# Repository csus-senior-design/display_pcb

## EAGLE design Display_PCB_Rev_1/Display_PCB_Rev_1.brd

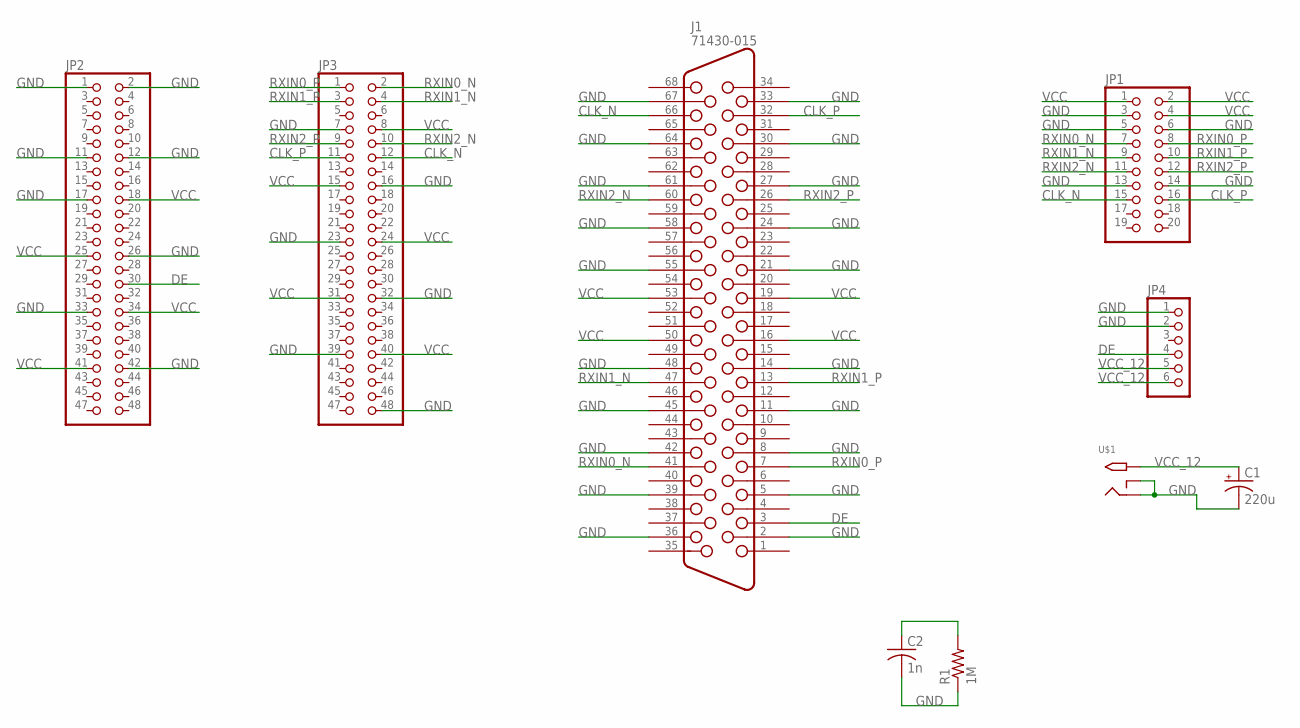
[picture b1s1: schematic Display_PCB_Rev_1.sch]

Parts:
C1: 220u; E5-8,5
C2: 1n; C0805
J1: 71430-015
JP1: PINHD-2X10M; 2X10M
JP2, JP3: PINHD-2X24; 2X24
JP4: PINHD-1X6M; 1X06M
R1: 1M; R0805W
U$1: 2.1MMJACKTHM; PJ-102A

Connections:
CLK_N: J1.66, JP1.15, JP3.12
CLK_P: J1.32, JP1.16, JP3.11
DE: J1.3, JP2.30, JP4.4
GND: C1.-, C2.2, J1.2, J1.5, J1.8, J1.11, J1.14, J1.21, J1.24, J1.27, J1.30, J1.33, J1.36, J1.39, J1.42, J1.45, J1.48, J1.55, J1.58, J1.61, J1.64, J1.67, JP1.3, JP1.5, JP1.6, JP1.13, JP1.14, JP2.1, JP2.2, JP2.11, JP2.12, JP2.17, JP2.26, JP2.33, JP2.42, JP3.7, JP3.16, JP3.23, JP3.32, JP3.39, JP3.48, JP4.1, JP4.2, R1.1, U$1.RING, U$1.RING_SW
unnamed: C2.1, R1.2
RXIN0_N: J1.41, JP1.7, JP3.2
RXIN0_P: J1.7, JP1.8, JP3.1
RXIN1_N: J1.47, JP1.9, JP3.4
RXIN1_P: J1.13, JP1.10, JP3.3
RXIN2_N: J1.60, JP1.11, JP3.10
RXIN2_P: J1.26, JP1.12, JP3.9
VCC: J1.16, J1.19, J1.50, J1.53, JP1.1, JP1.2, JP1.4, JP2.18, JP2.25, JP2.34, JP2.41, JP3.8, JP3.15, JP3.24, JP3.31, JP3.40
VCC_12: C1.+, JP4.5, JP4.6, U$1.TIP

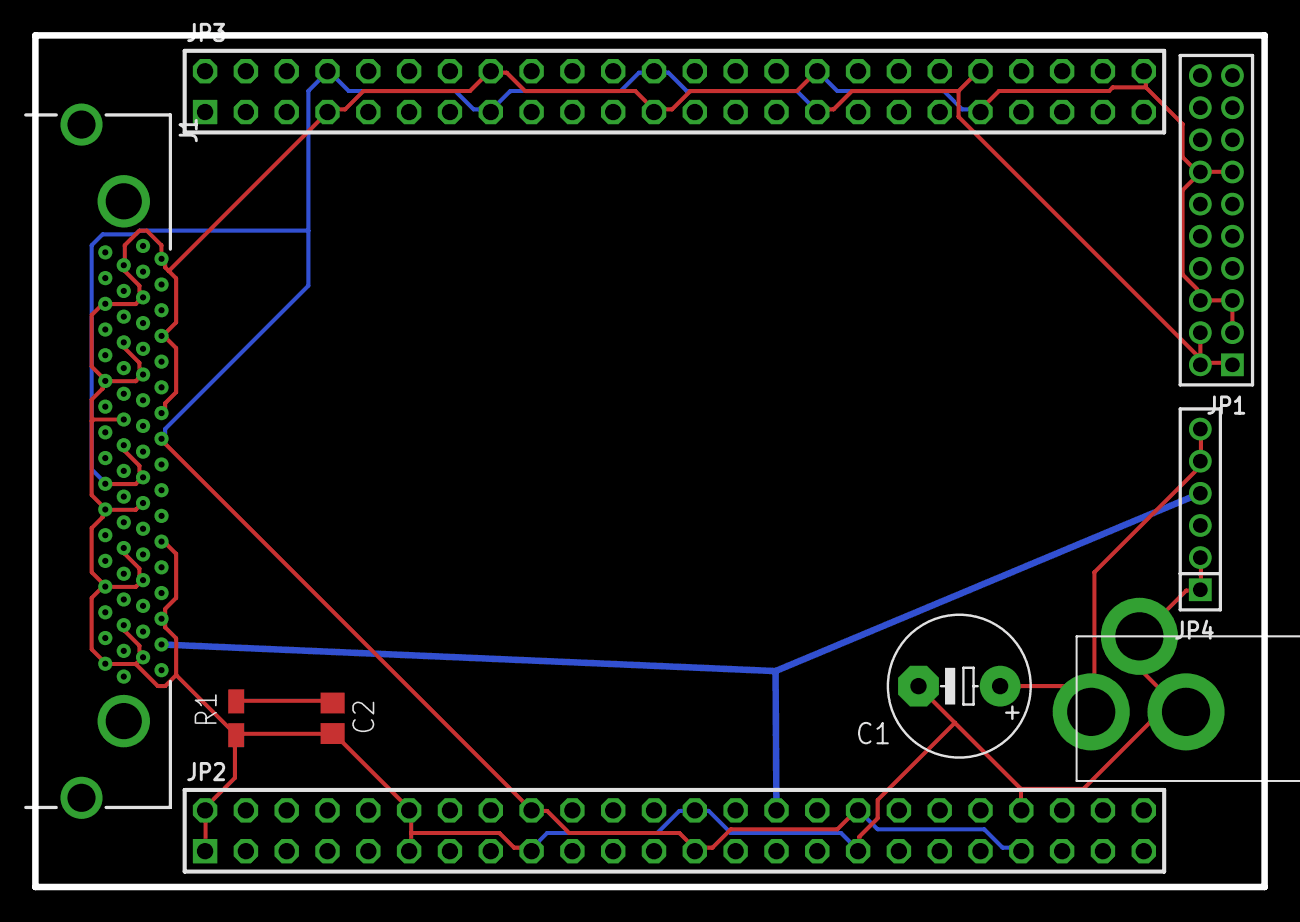
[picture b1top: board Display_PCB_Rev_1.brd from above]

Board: 4 copper layers, 76.5 x 53.0 mm, 9 parts (0 on the bottom side), 13 nets.

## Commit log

2015-08-17 Moved Rev1 of PCB from Google Drive to github
2015-08-23 Cleaned up schematic and layout; Added DC Barrel Jack and coupling capacitor; filtering circuit for shield
2015-08-23 Added .gitignore; removed unnecessary files; added routes for VCC, GND, and VCC_12
2015-08-23 removed .pro file
2015-08-23 Updated eagle project file
2015-08-26 first set of differential pairs
2015-08-27 Starting the wiring of the VHDCI connections
2015-08-31 Loaded Dirty PCBs Design Rules
2015-08-31 Ripped up old differential signal routes, and added in start of new route with smaller trace width.
2015-09-01 First Diff Pair VHDCI
2015-09-02 VHDCI diff signals wired, not matched lengths though
2015-09-02 VHDCI Connector finished and matched length
2015-09-02 VHDCI matched signal length, and Scarab signals wired not matched length
2015-09-02 All Differential Pairs with matched lengths

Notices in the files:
parts and their libraries:
con-molex-vhdci: Copyright (C) 2015, Bob Starr
